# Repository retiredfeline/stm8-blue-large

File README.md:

## Large STM8S103F3P6 development board

This is a large version of the STM8 "Blue Pill", not to be confused with the STM32 "Blue Pill". I designed this mainly to get more connection points: 2 header pads for each STM8 pin, 4 sets of power supply headers for connecting peripherals, and 2 uncommitted tactile button positions. Small size wasn't important to me; I wanted something to build gadgets using the STM8S103F3P6 chips I had.

The jumper bridge between +5v ad +3.3V is used when you want to run the MCU at 5V, perhaps to connect to 5V peripherals. For downloading the firmware to the MCU, the STlink dongle will provide 3.3V. Do not connect both the dongle and the micro-USB power at the same time.

This is a mixed design. The capacitors are SMT while the resistors and LEDs are THT; they were what I had handy. The micro-USB connector is an adaptor you can buy from the usual outlets for easier soldering. The MCU footprint is hybrid: there are TSSOP-20 pads but also 20 THT pads for an adaptor board so that you or a skilled friend can solder that separately.

Thus I don't expect that the design will suit everybody or even anybody as is, but I'm publishing it so that people can have KiCad design info to remix into their own design.

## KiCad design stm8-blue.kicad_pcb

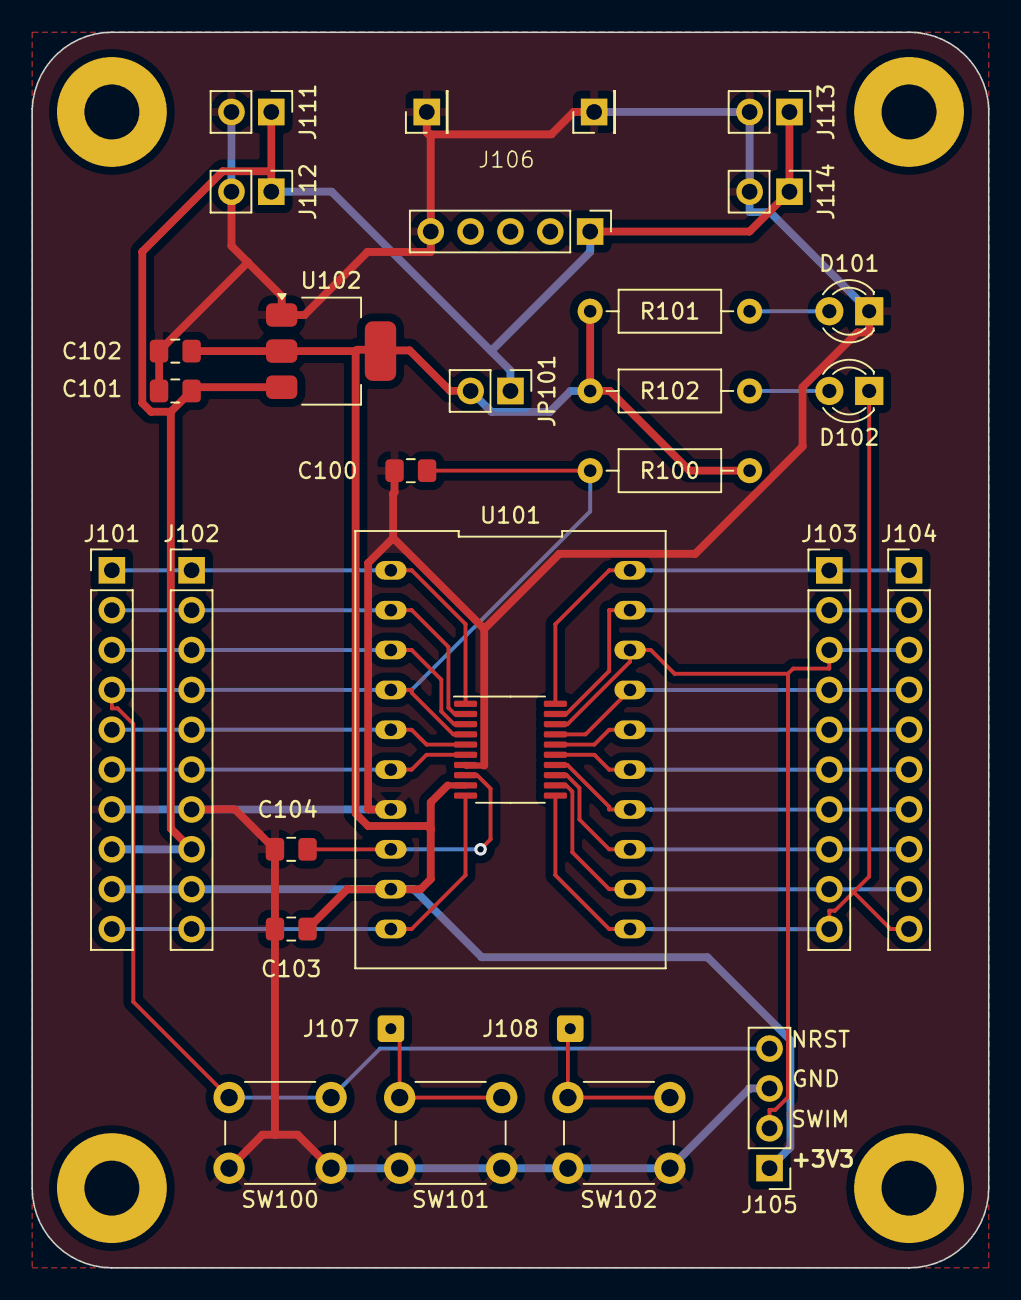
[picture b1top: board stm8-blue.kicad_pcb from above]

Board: 2 copper layers, 61.0 x 78.7 mm, 32 parts (0 on the bottom side), 25 nets.

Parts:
C100, C101, C102, C103: 0.1uF; C_0805_2012Metric_Pad1.18x1.45mm_HandSolder
C104: 1uF; C_0805_2012Metric_Pad1.18x1.45mm_HandSolder
D101: PWR; LED_D3.0mm
D102: TEST; LED_D3.0mm
H101, H102, H103, H104: MountingHole; MountingHole_3.5mm_Pad
J101, J102: Header 1; PinHeader_1x10_P2.54mm_Vertical
J103, J104: Header 2; PinHeader_1x10_P2.54mm_Vertical
J105: Program; PinHeader_1x04_P2.54mm_Vertical
J106: USB_B_Micro; USB Micro power
J107: Switch 1; SolderWire-0.127sqmm_1x01_D0.48mm_OD1mm
J108: Switch 2; SolderWire-0.127sqmm_1x01_D0.48mm_OD1mm
J111, J112, J113, J114: POWER; PinHeader_1x02_P2.54mm_Vertical
JP101: BYPASS; PinHeader_1x02_P2.54mm_Vertical
R100: 10K; R_Axial_DIN0207_L6.3mm_D2.5mm_P10.16mm_Horizontal
R101, R102: 1K; R_Axial_DIN0207_L6.3mm_D2.5mm_P10.16mm_Horizontal
SW100: RST; SW_PUSH_6mm_H5mm
SW101: SW1; SW_PUSH_6mm_H5mm
SW102: SW2; SW_PUSH_6mm_H5mm
U101: STM8S103F3P6; DIP_TSSOP-20_600_ELL
U102: AMS1117-3.3; SOT-223-3_TabPin2

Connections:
+3.3V: C102.2, C103.1, J101.9, J102.9, J105.1, JP101.2 (B), R100.2, R101.1, R102.2, U101.9 (VDD), U102.2 (VO)
+5V: C101.2, J101.8, J102.8, J106.1 (VBUS), J111.1, J112.1, J113.1, J114.1, JP101.1 (A), U102.3 (VI)
/NRST: C100.2, J101.4, J102.4, J105.4, R100.1, SW100.2 (B), U101.4 (NRST)
/PA1: J101.5, J102.5, U101.5 (PA1)
/PA2: J101.6, J102.6, U101.6 (PA2)
/PA3: J101.10, J102.10, U101.10 (PA3)
/PB4: J103.9, J104.9, U101.12 (PB4)
/PB5: D102.1 (K), J103.10, J104.10, U101.11 (PB5)
/PC3: J103.8, J104.8, U101.13 (PC3)
/PC4: J103.7, J104.7, U101.14 (PC4)
/PC5: J103.6, J104.6, U101.15 (PC5)
/PC6: J103.5, J104.5, U101.16 (PC6)
/PC7: J103.4, J104.4, U101.17 (PC7)
/PD1: J103.3, J104.3, J105.2, U101.18 (PD1)
/PD2: J103.2, J104.2, U101.19 (PD2)
/PD3: J103.1, J104.1, U101.20 (PD3)
/PD4: J101.1, J102.1, U101.1 (PD4)
/PD5: J101.2, J102.2, U101.2 (PD5)
/PD6: J101.3, J102.3, U101.3 (PD6)
GND: C100.1, C101.1, C102.1, C103.2, C104.1, D101.1 (K), J101.7, J102.7, J105.3, J106.5 (GND), J106.6 (Shield), J111.2, J112.2, J113.2, J114.2, SW100.1 (A), SW101.1 (A), SW102.1 (A), U101.7 (VSS), U102.1 (GND)
unnamed: D101.2 (A), R101.2
unnamed: D102.2 (A), R102.1
unnamed: J107.1, SW101.2 (B)
unnamed: J108.1, SW102.2 (B)
unnamed: C104.2, U101.8 (VCAP)

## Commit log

2024-09-29 Initial checkin
